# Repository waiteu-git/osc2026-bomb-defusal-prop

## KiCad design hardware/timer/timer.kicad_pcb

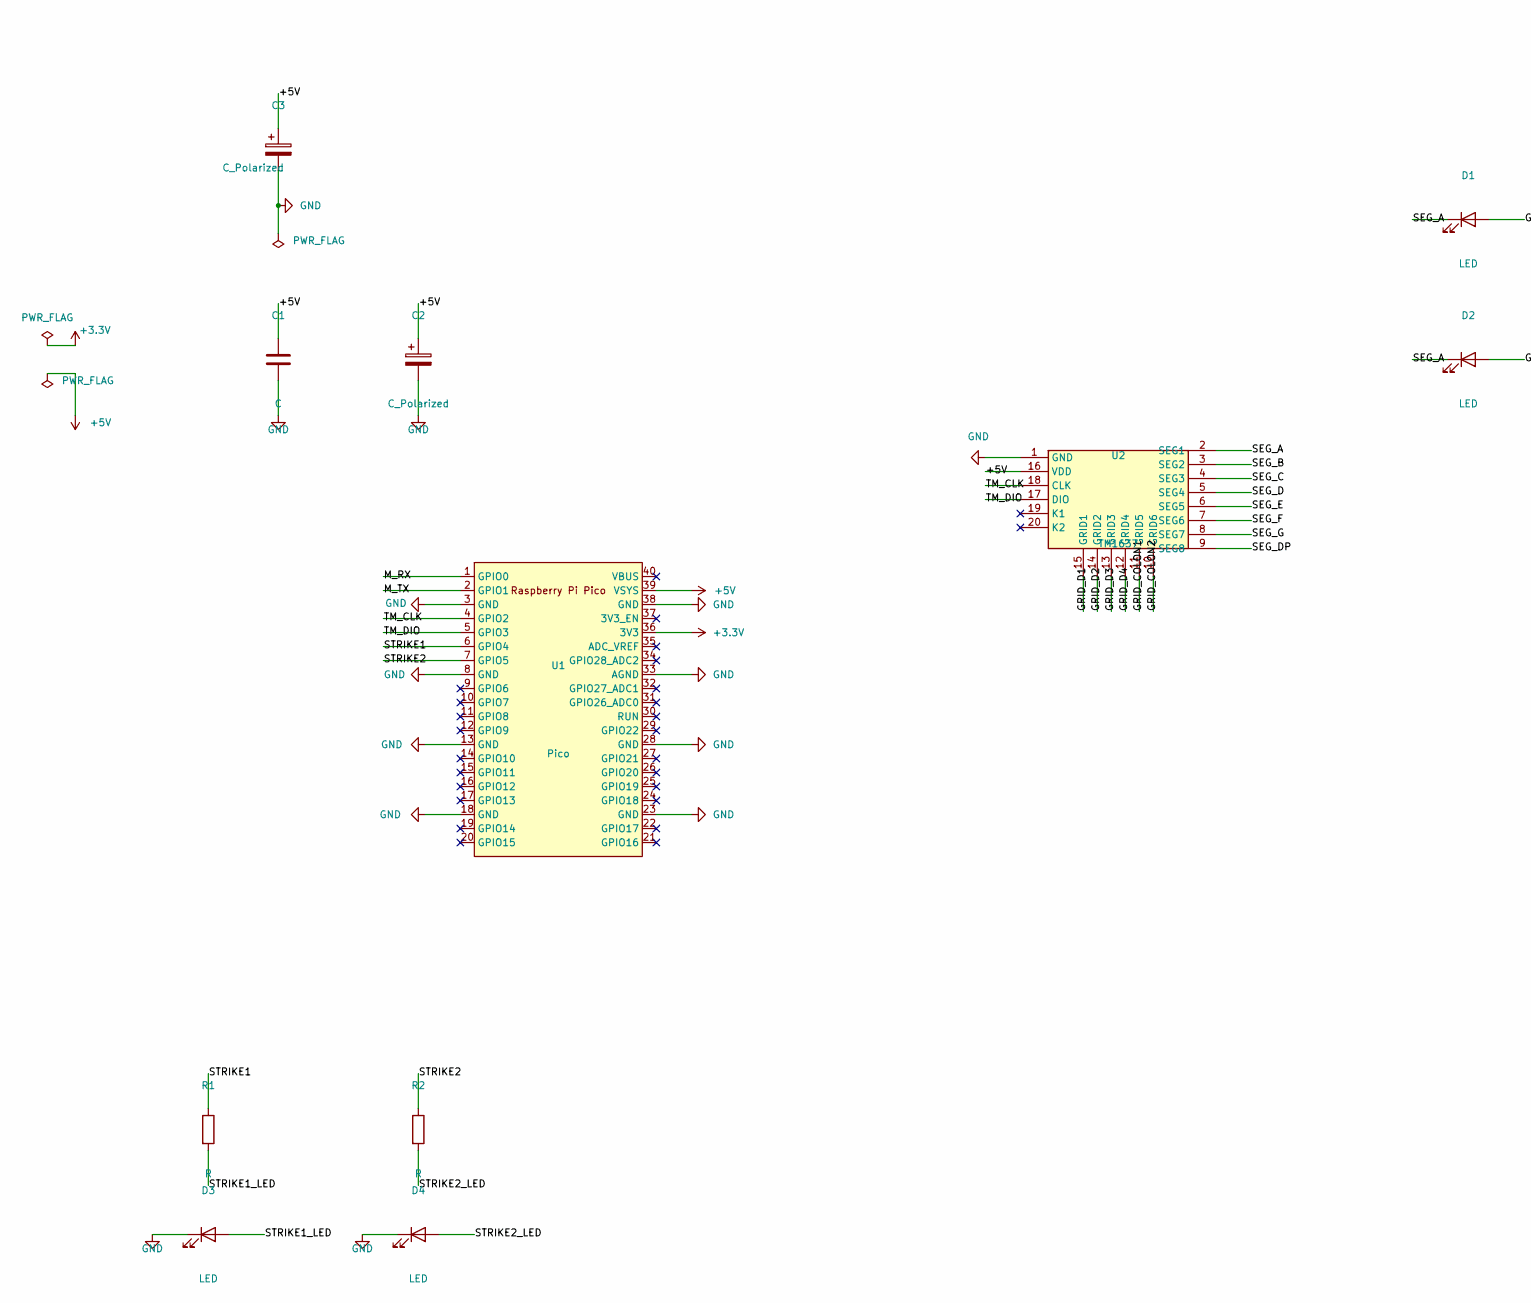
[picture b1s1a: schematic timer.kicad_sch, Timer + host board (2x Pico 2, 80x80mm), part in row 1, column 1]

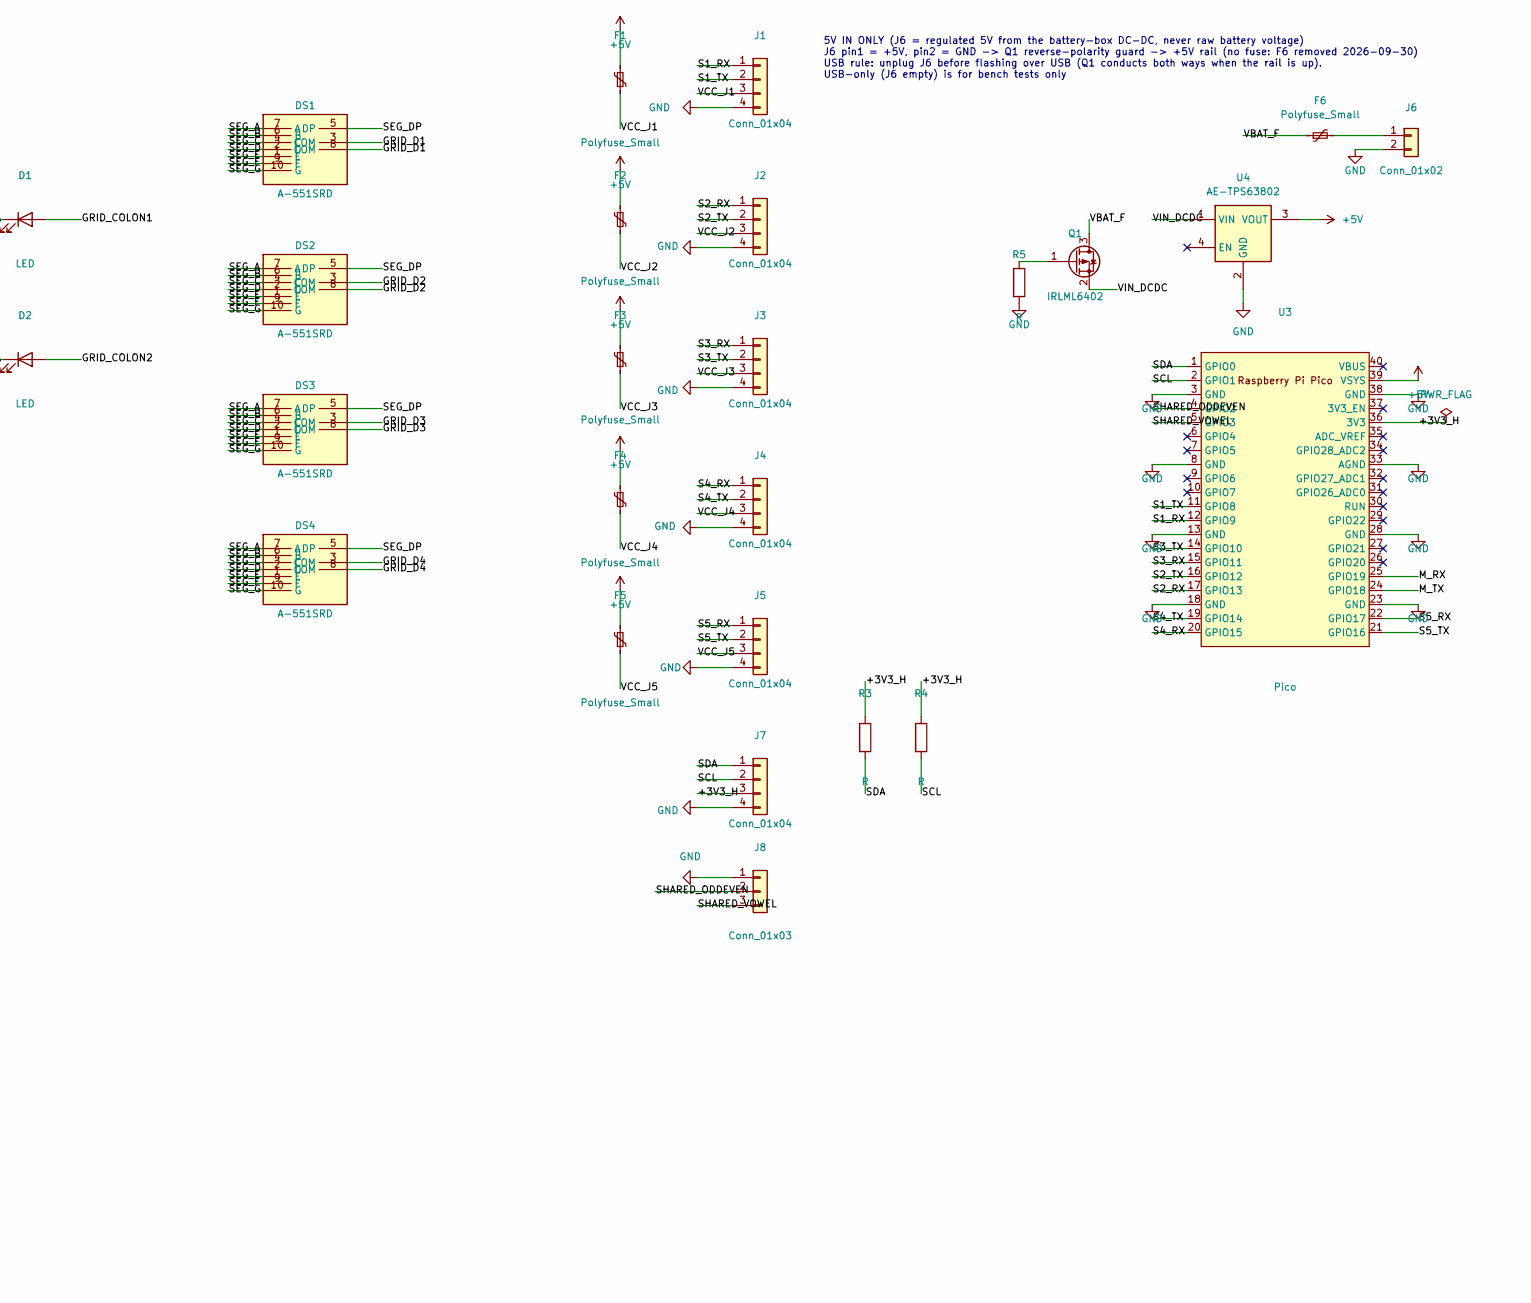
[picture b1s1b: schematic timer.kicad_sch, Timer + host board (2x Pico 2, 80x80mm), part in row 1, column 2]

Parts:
C1: C; C_Disc_D5.0mm_W2.5mm_P2.50mm
C2: C_Polarized; CP_Radial_D5.0mm_P2.00mm
C3: C_Polarized; CP_Radial_D8.0mm_P3.50mm
D1, D2: LED; LED_D3.0mm
D3, D4: LED; LED_D5.0mm
DS1, DS2, DS3, DS4: A-551SRD
F1, F2, F3, F4, F5: Polyfuse_Small; MF-RX030_Radial_P5.10mm
F6: Polyfuse_Small; MF-R185_Radial_P5.10mm
J1, J2, J3, J4, J5, J7: Conn_01x04; JST_XH_B4B-XH-A_1x04_P2.50mm_Vertical
J6: Conn_01x02; JST_XH_B2B-XH-A_1x02_P2.50mm_Vertical
J8: Conn_01x03; JST_XH_B3B-XH-A_1x03_P2.50mm_Vertical
Q1: IRLML6402; SOT-23
R1, R2: R; R_Axial_DIN0207_L6.3mm_D2.5mm_P10.16mm_Horizontal
R3, R4, R5: R; R_Axial_DIN0207_L6.3mm_D2.5mm_P2.54mm_Vertical
U1, U3: Pico; RPi_Pico_TH_Headers
U2: TM1637; DIP-20_W7.62mm
U4: AE-TPS63802

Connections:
+3.3V: U1.36 (3V3)
+5V: C1.1, C2.1, C3.1, F1.1, F2.1, F3.1, F4.1, F5.1, U1.39 (VSYS), U2.16 (VDD), U3.39 (VSYS), U4.3 (VOUT)
/+3V3_H: J7.3, R3.1, R4.1, U3.36 (3V3)
/GRID_COLON1: D1.2 (A), U2.11 (GRID5)
/GRID_COLON2: D2.2 (A), U2.10 (GRID6)
/GRID_D1: DS1.3 (COM), DS1.8 (COM), U2.15 (GRID1)
/GRID_D2: DS2.3 (COM), DS2.8 (COM), U2.14 (GRID2)
/GRID_D3: DS3.3 (COM), DS3.8 (COM), U2.13 (GRID3)
/GRID_D4: DS4.3 (COM), DS4.8 (COM), U2.12 (GRID4)
/M_RX: U1.1 (GPIO0), U3.25 (GPIO19)
/M_TX: U1.2 (GPIO1), U3.24 (GPIO18)
/S1_RX: J1.1, U3.12 (GPIO9)
/S1_TX: J1.2, U3.11 (GPIO8)
/S2_RX: J2.1, U3.17 (GPIO13)
/S2_TX: J2.2, U3.16 (GPIO12)
/S3_RX: J3.1, U3.15 (GPIO11)
/S3_TX: J3.2, U3.14 (GPIO10)
/S4_RX: J4.1, U3.20 (GPIO15)
/S4_TX: J4.2, U3.19 (GPIO14)
/S5_RX: J5.1, U3.22 (GPIO17)
/S5_TX: J5.2, U3.21 (GPIO16)
/SCL: J7.2, R4.2, U3.2 (GPIO1)
/SDA: J7.1, R3.2, U3.1 (GPIO0)
/SEG_A: D1.1 (K), D2.1 (K), DS1.7 (A), DS2.7 (A), DS3.7 (A), DS4.7 (A), U2.2 (SEG1)
/SEG_B: DS1.6 (B), DS2.6 (B), DS3.6 (B), DS4.6 (B), U2.3 (SEG2)
/SEG_C: DS1.4 (C), DS2.4 (C), DS3.4 (C), DS4.4 (C), U2.4 (SEG3)
/SEG_D: DS1.2 (D), DS2.2 (D), DS3.2 (D), DS4.2 (D), U2.5 (SEG4)
/SEG_DP: DS1.5 (DP), DS2.5 (DP), DS3.5 (DP), DS4.5 (DP), U2.9 (SEG8)
/SEG_E: DS1.1 (E), DS2.1 (E), DS3.1 (E), DS4.1 (E), U2.6 (SEG5)
/SEG_F: DS1.9 (F), DS2.9 (F), DS3.9 (F), DS4.9 (F), U2.7 (SEG6)
/SEG_G: DS1.10 (G), DS2.10 (G), DS3.10 (G), DS4.10 (G), U2.8 (SEG7)
/SHARED_ODDEVEN: J8.2, U3.4 (GPIO2)
/SHARED_VOWEL: J8.3, U3.5 (GPIO3)
/STRIKE1: R1.1, U1.6 (GPIO4)
/STRIKE1_LED: D3.2 (A), R1.2
/STRIKE2: R2.1, U1.7 (GPIO5)
/STRIKE2_LED: D4.2 (A), R2.2
/TM_CLK: U1.4 (GPIO2), U2.18 (CLK)
/TM_DIO: U1.5 (GPIO3), U2.17 (DIO)
/VBAT_F: F6.1, Q1.3 (D)
/VCC_J1: F1.2, J1.3
/VCC_J2: F2.2, J2.3
/VCC_J3: F3.2, J3.3
/VCC_J4: F4.2, J4.3
/VCC_J5: F5.2, J5.3
/VIN_DCDC: Q1.2 (S), U4.1 (VIN)
GND: C1.2, C2.2, C3.2, D3.1 (K), D4.1 (K), J1.4, J2.4, J3.4, J4.4, J5.4, J6.2, J7.4, J8.1, R5.2, U1.3 (GND), U1.8 (GND), U1.13 (GND), U1.18 (GND), U1.23 (GND), U1.28 (GND), U1.33 (AGND), U1.38 (GND), U2.1 (GND), U3.3 (GND), U3.8 (GND), U3.13 (GND), U3.18 (GND), U3.23 (GND), U3.28 (GND), U3.33 (AGND), U3.38 (GND), U4.2 (GND)
unnamed: F6.2, J6.1
unnamed: Q1.1 (G), R5.1

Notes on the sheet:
5V IN ONLY (J6 = regulated 5V from the battery-box DC-DC, never raw battery voltage) J6 pin1 = +5V, pin2 = GND -> Q1 reverse-polarity guard -> +5V rail (no fuse: F6 removed 2026-09-30) USB rule: unplug J6 before flashing over USB (Q1 conducts both ways when the rail is up). USB-only (J6 empty) is f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

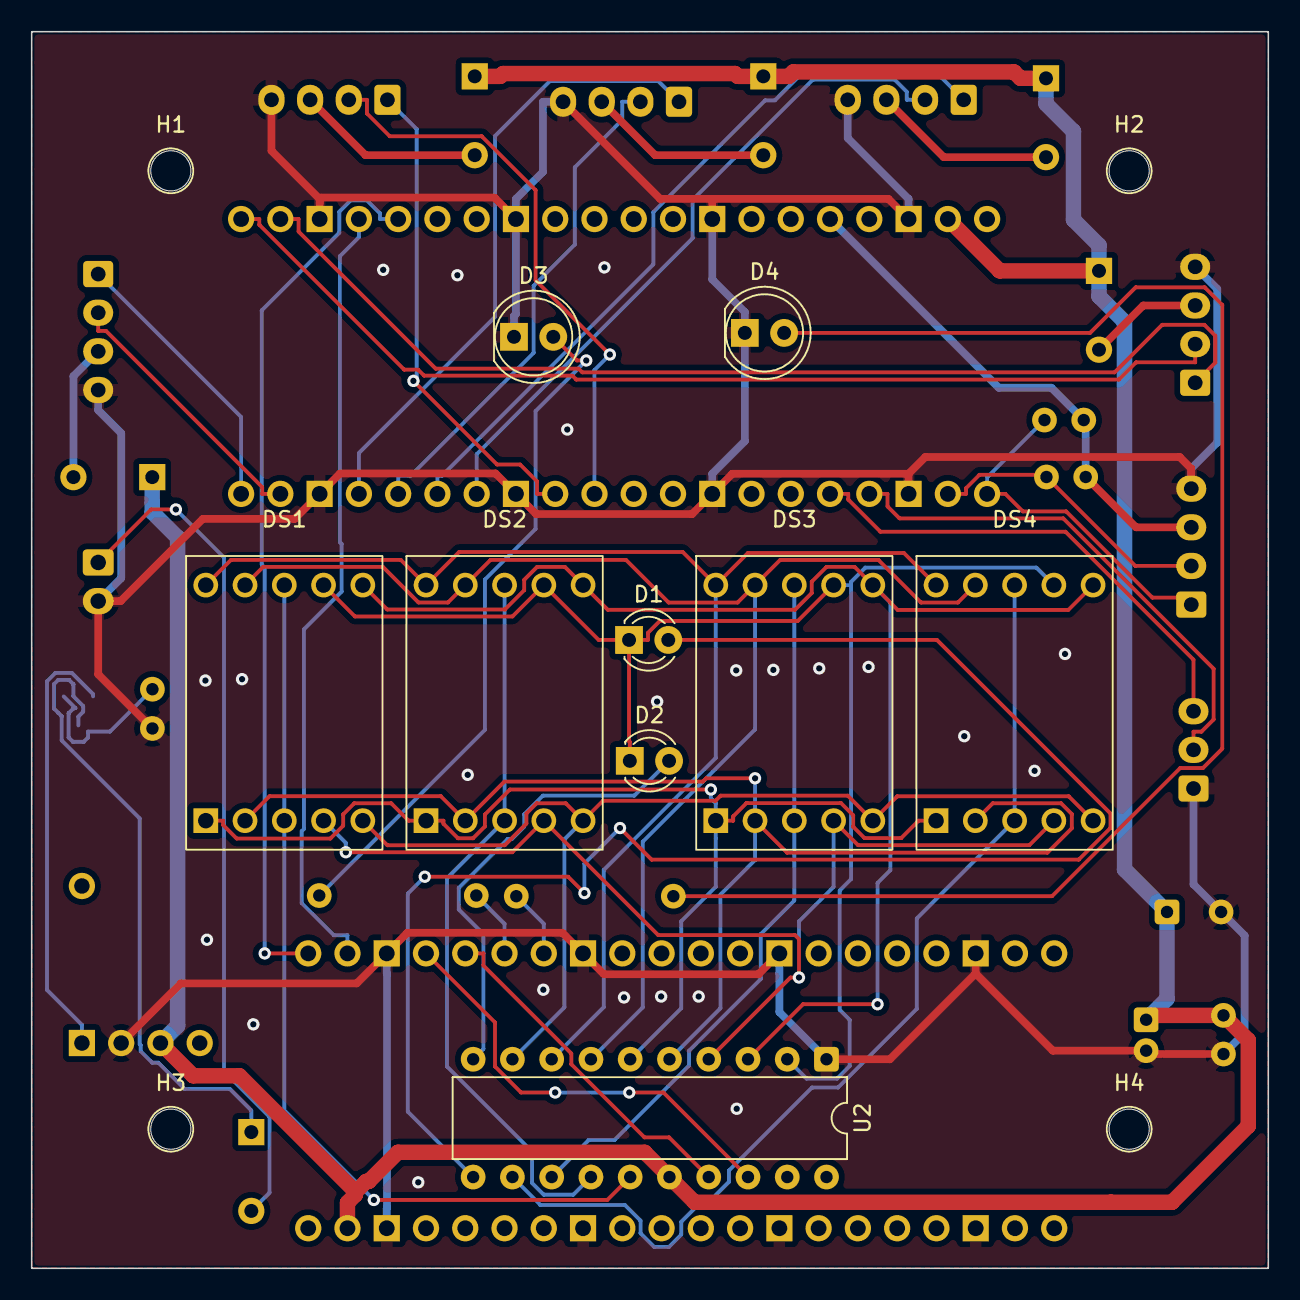
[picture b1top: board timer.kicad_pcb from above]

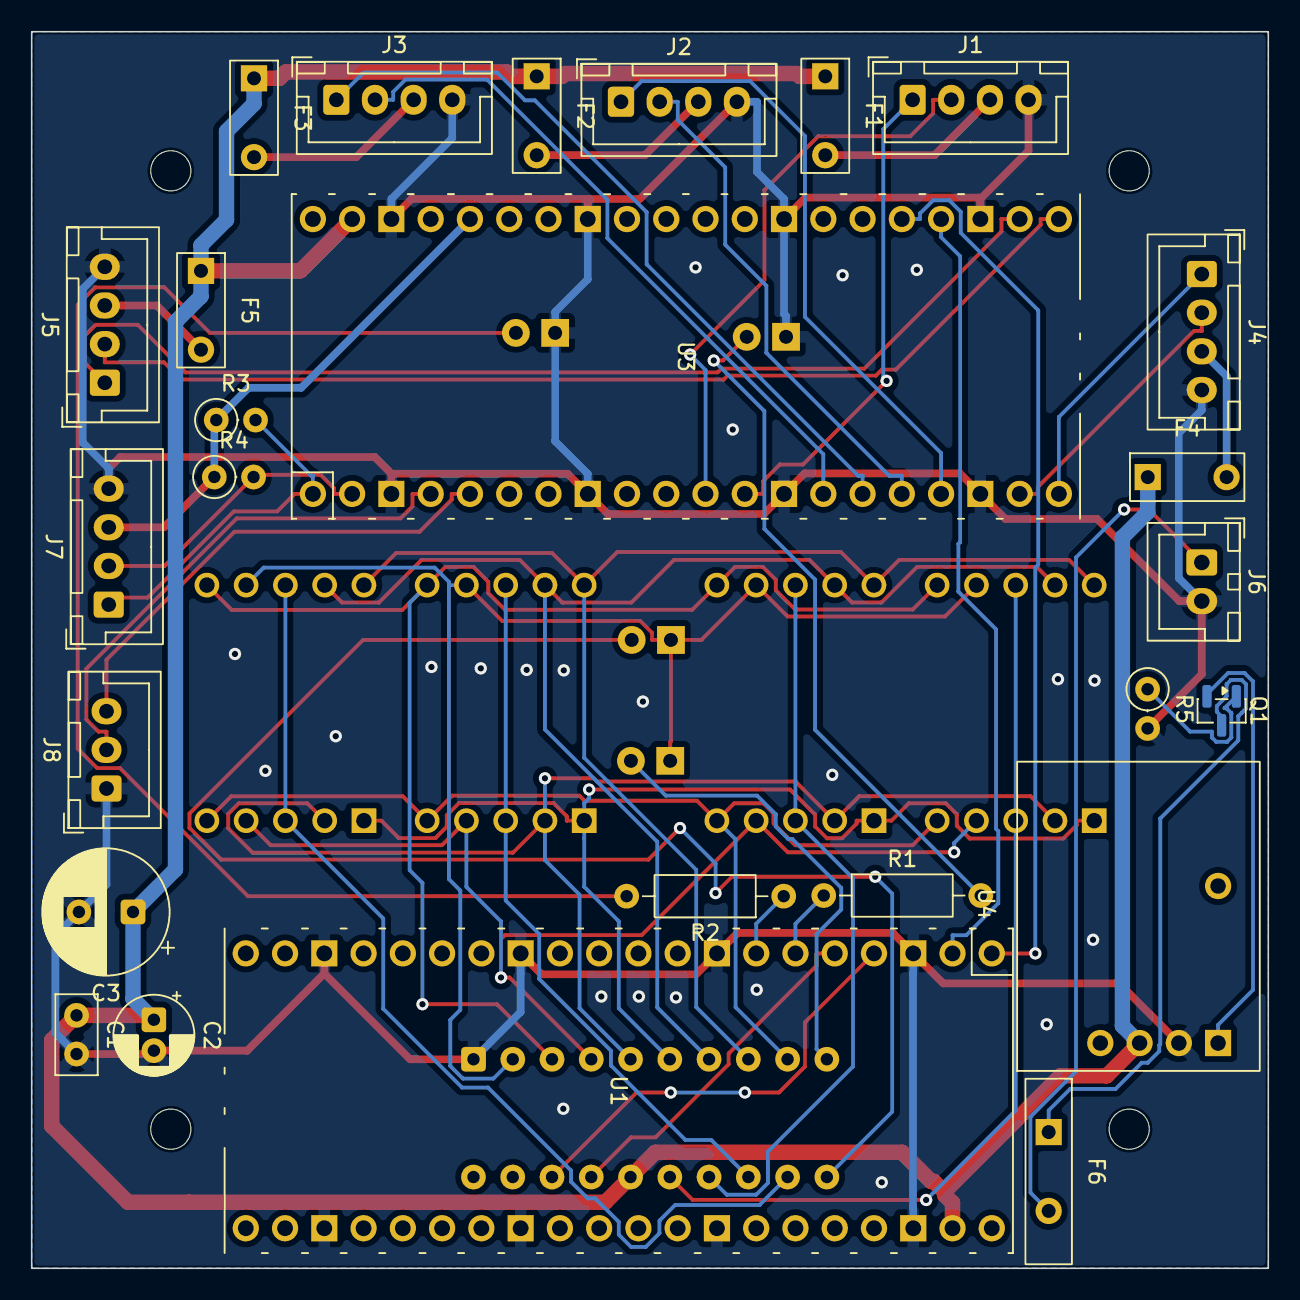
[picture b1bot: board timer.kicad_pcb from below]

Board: 2 copper layers, 80.0 x 80.0 mm, 39 parts (26 on the bottom side), 48 nets.

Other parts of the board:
H1, H2, H3, H4: M2.6 hole (dia 2.6mm); MountingHole_2.6mm

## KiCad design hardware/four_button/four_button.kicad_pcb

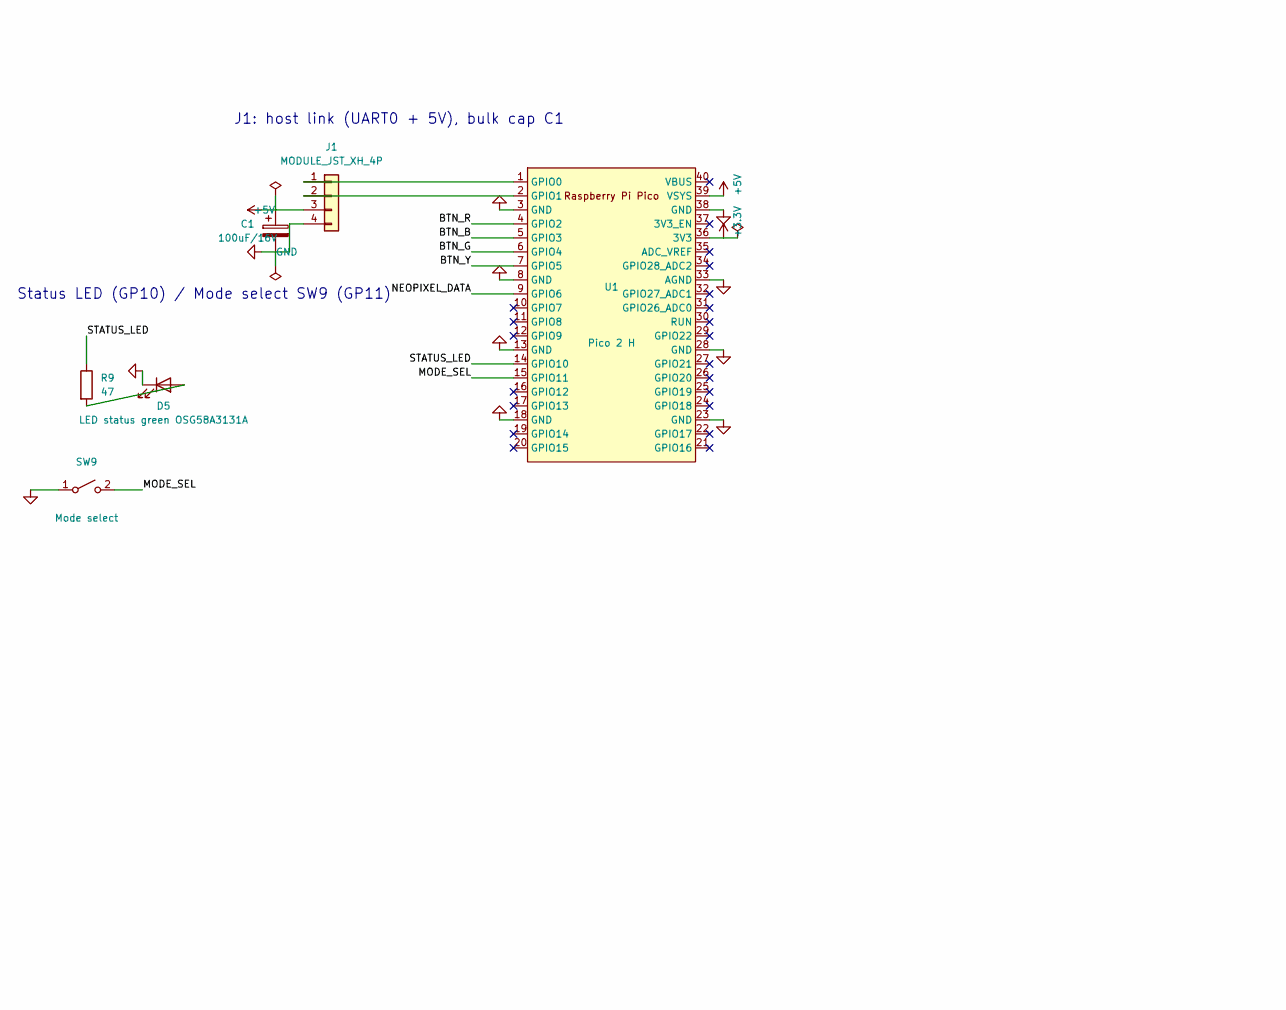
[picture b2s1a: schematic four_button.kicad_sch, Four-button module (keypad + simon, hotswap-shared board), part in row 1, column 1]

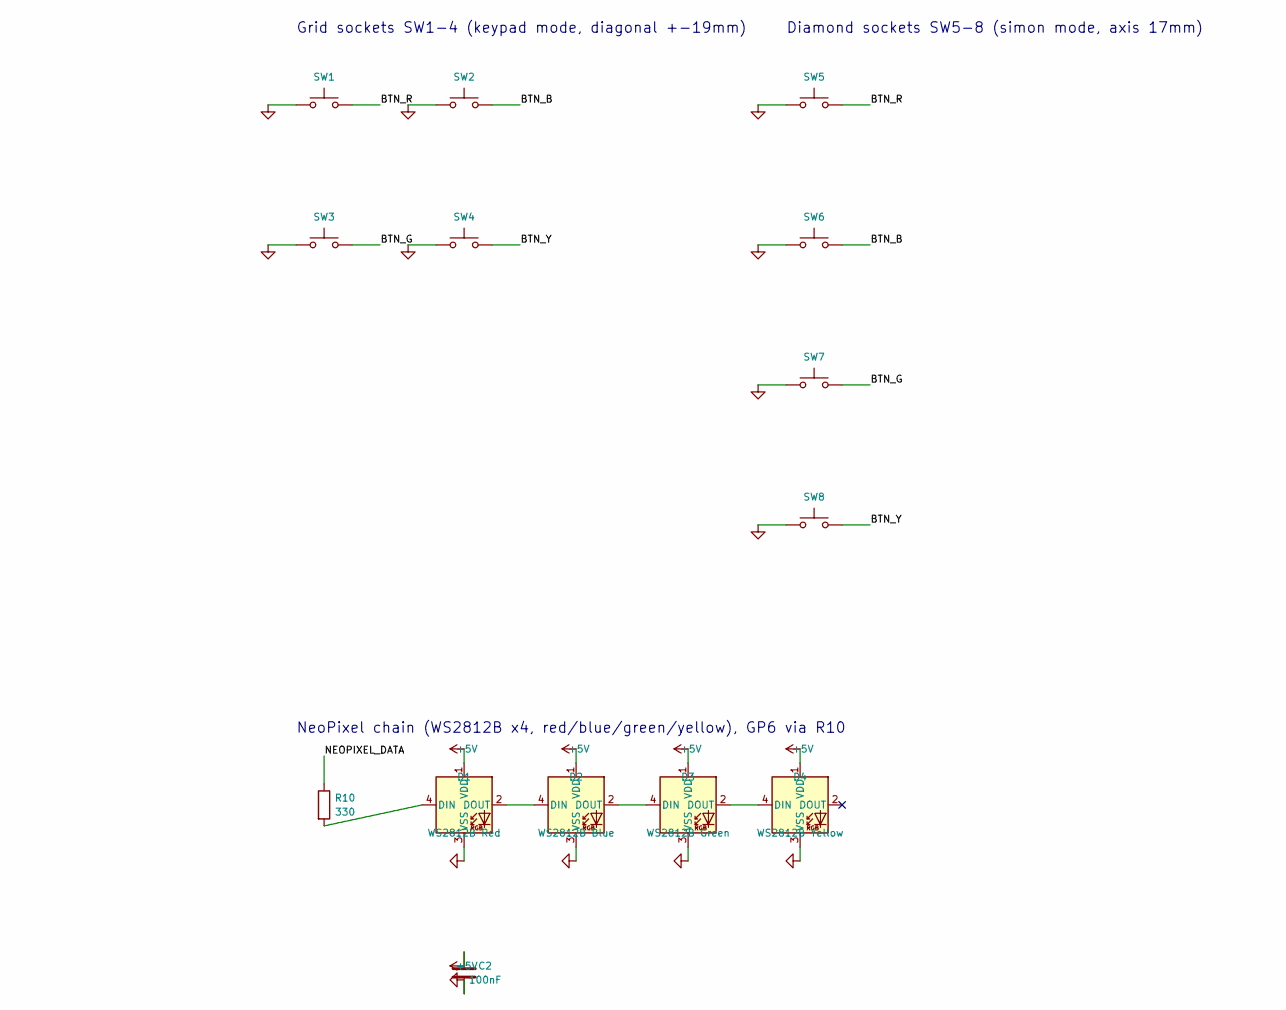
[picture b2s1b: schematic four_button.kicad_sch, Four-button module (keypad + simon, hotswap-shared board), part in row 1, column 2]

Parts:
C1: 100uF/16V; CP_Radial_D6.3mm_P2.50mm
C2: 100nF; C_Disc_D3.0mm_W2.0mm_P2.50mm
D1: WS2812B Red; LED_WS2812B_PLCC4_5.0x5.0mm_P3.2mm
D2: WS2812B Blue; LED_WS2812B_PLCC4_5.0x5.0mm_P3.2mm
D3: WS2812B Green; LED_WS2812B_PLCC4_5.0x5.0mm_P3.2mm
D4: WS2812B Yellow; LED_WS2812B_PLCC4_5.0x5.0mm_P3.2mm
D5: LED status green OSG58A3131A; LED_D3.0mm
J1: MODULE_JST_XH_4P; JST_XH_B4B-XH-A_1x04_P2.50mm_Vertical
R9: 47; R_Axial_DIN0207_L6.3mm_D2.5mm_P7.62mm_Horizontal
R10: 330; R_Axial_DIN0207_L6.3mm_D2.5mm_P7.62mm_Horizontal
SW1, SW2, SW3, SW4, SW5, SW6, SW7, SW8: Kailh_socket_MX
SW9: Mode select; SW_Slide_2P
U1: Pico 2 H; RPi_Pico_TH_Headers

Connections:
+3.3V: U1.36 (3V3)
+5V: C1.1, C2.1, D1.1 (VDD), D2.1 (VDD), D3.1 (VDD), D4.1 (VDD), J1.3, U1.39 (VSYS)
/BTN_B: SW2.2, SW6.2, U1.5 (GPIO3)
/BTN_G: SW3.2, SW7.2, U1.6 (GPIO4)
/BTN_R: SW1.2, SW5.2, U1.4 (GPIO2)
/BTN_Y: SW4.2, SW8.2, U1.7 (GPIO5)
/MODE_SEL: SW9.2 (B), U1.15 (GPIO11)
/NEOPIXEL_DATA: R10.1, U1.9 (GPIO6)
/STATUS_LED: R9.1, U1.14 (GPIO10)
GND: C1.2, C2.2, D1.3 (VSS), D2.3 (VSS), D3.3 (VSS), D4.3 (VSS), D5.1 (K), J1.4, SW1.1, SW2.1, SW3.1, SW4.1, SW5.1, SW6.1, SW7.1, SW8.1, SW9.1 (A), U1.3 (GND), U1.8 (GND), U1.13 (GND), U1.18 (GND), U1.23 (GND), U1.28 (GND), U1.33 (AGND), U1.38 (GND)
unnamed: D1.4 (DIN), R10.2
unnamed: D1.2 (DOUT), D2.4 (DIN)
unnamed: D2.2 (DOUT), D3.4 (DIN)
unnamed: D3.2 (DOUT), D4.4 (DIN)
unnamed: D5.2 (A), R9.2
unnamed: J1.1, U1.1 (GPIO0)
unnamed: J1.2, U1.2 (GPIO1)

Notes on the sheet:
J1: host link (UART0 + 5V), bulk cap C1
Grid sockets SW1-4 (keypad mode, diagonal +-19mm)
Diamond sockets SW5-8 (simon mode, axis 17mm)
NeoPixel chain (WS2812B x4, red/blue/green/yellow), GP6 via R10
Status LED (GP10) / Mode select SW9 (GP11)

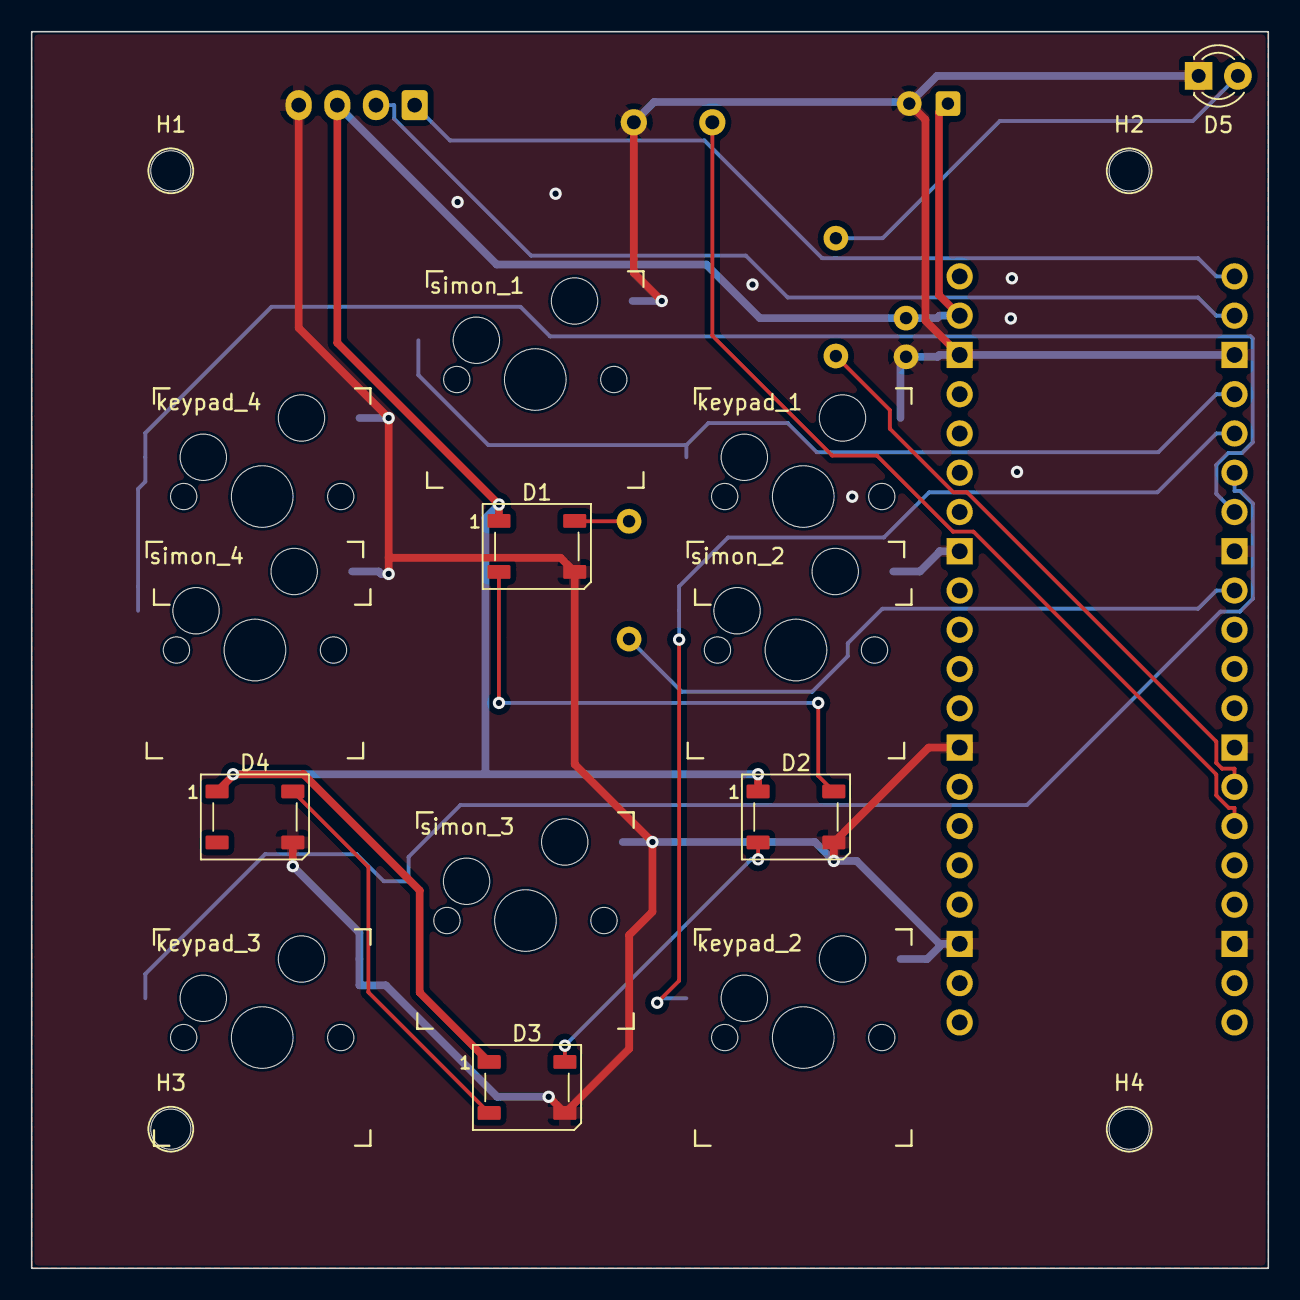
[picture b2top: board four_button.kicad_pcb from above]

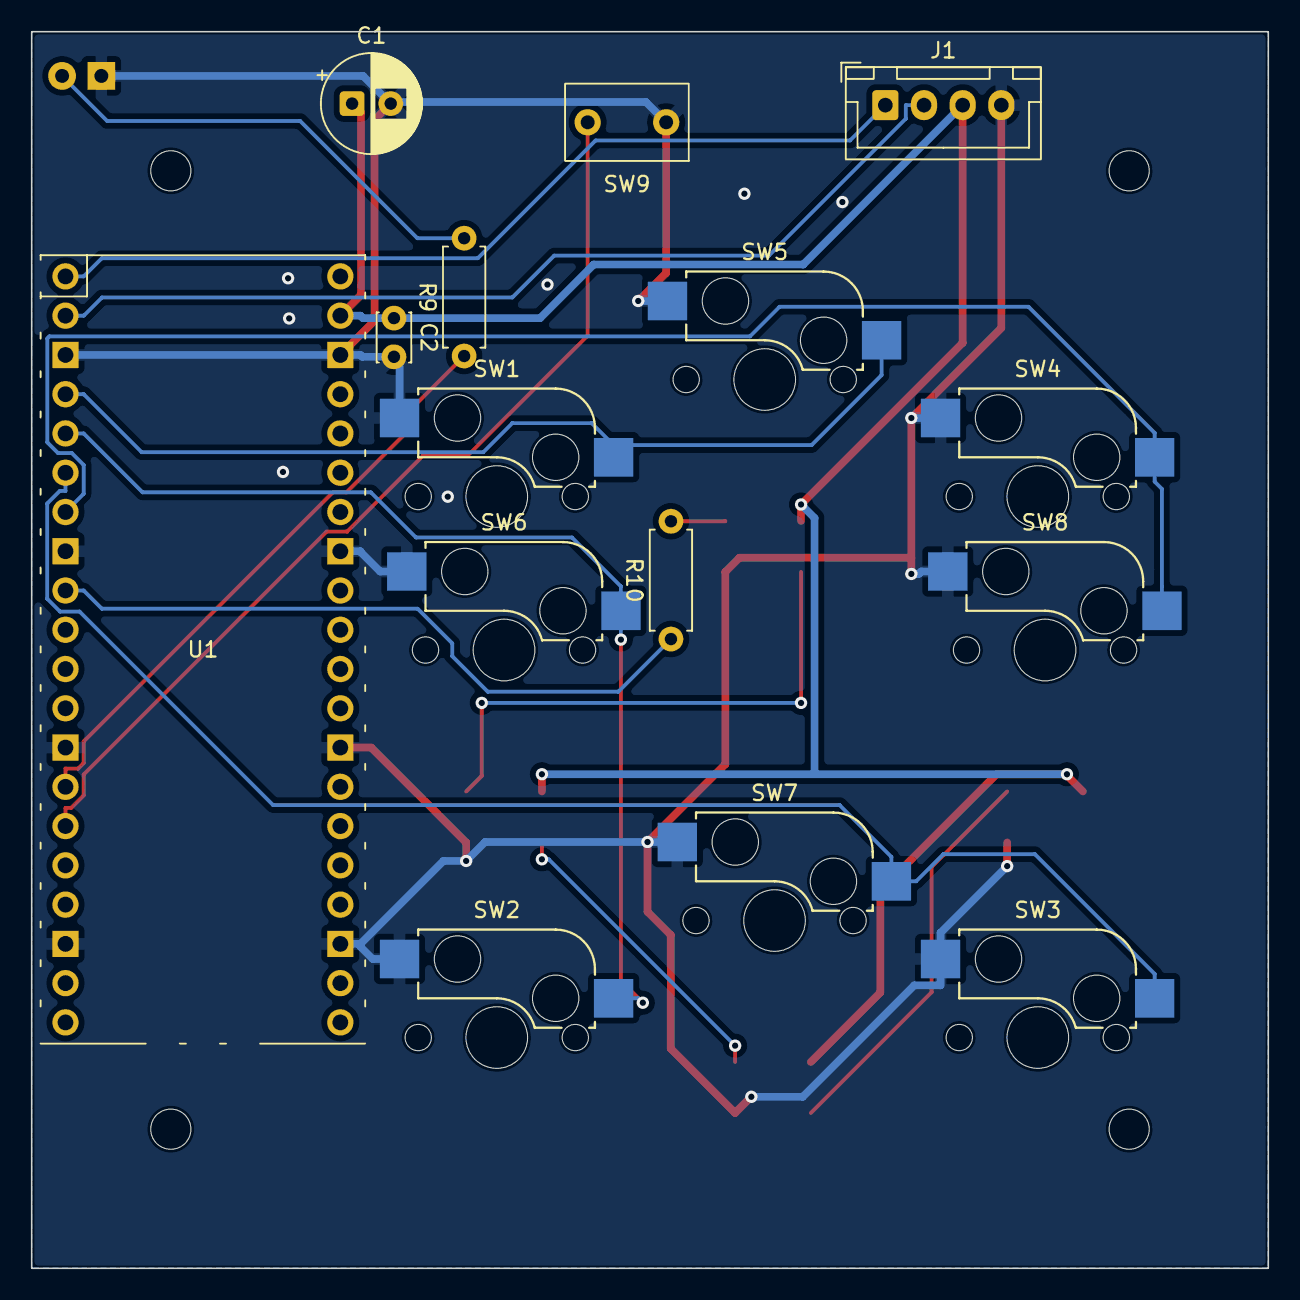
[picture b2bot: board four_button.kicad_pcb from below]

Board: 2 copper layers, 80.0 x 80.0 mm, 24 parts (7 on the bottom side), 16 nets.

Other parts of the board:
H1, H2, H3, H4: M2.6 hole (dia 2.6mm); MountingHole_2.6mm

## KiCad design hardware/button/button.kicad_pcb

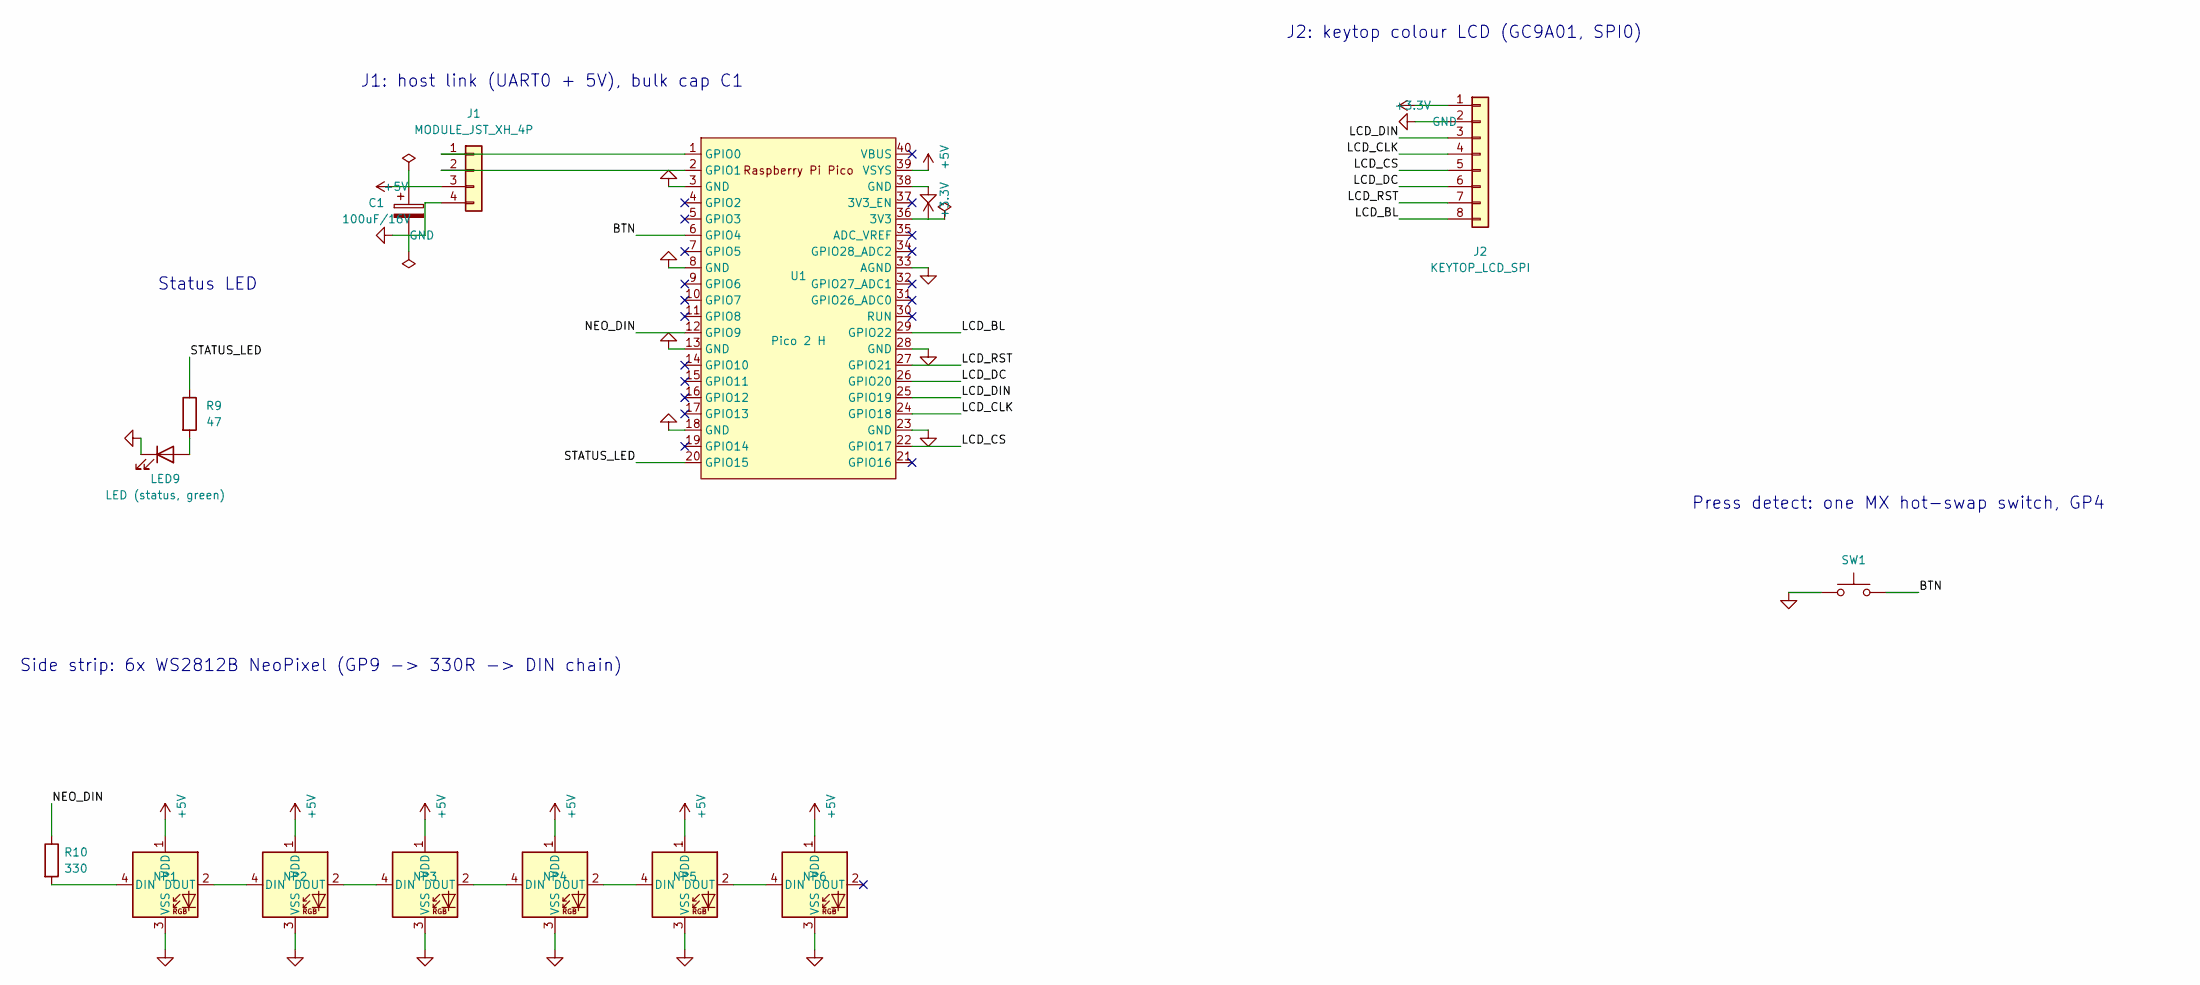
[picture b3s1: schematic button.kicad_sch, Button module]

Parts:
C1: 100uF/16V; CP_Radial_D6.3mm_P2.50mm
J1: MODULE_JST_XH_4P; JST_XH_B4B-XH-A_1x04_P2.50mm_Vertical
J2: KEYTOP_LCD_SPI; PinHeader_1x08_P2.54mm_Vertical
LED9: LED (status, green); LED_D3.0mm
NP1, NP2, NP3, NP4, NP5, NP6: WS2812B; LED_WS2812B_PLCC4_5.0x5.0mm_P3.2mm
R9: 47; R_Axial_DIN0207_L6.3mm_D2.5mm_P7.62mm_Horizontal
R10: 330; R_Axial_DIN0207_L6.3mm_D2.5mm_P7.62mm_Horizontal
SW1: SW_Push; Kailh_socket_MX
U1: Pico 2 H; RPi_Pico_TH_Headers

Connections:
+3.3V: J2.1, U1.36 (3V3)
+5V: C1.1, J1.3, NP1.1 (VDD), NP2.1 (VDD), NP3.1 (VDD), NP4.1 (VDD), NP5.1 (VDD), NP6.1 (VDD), U1.39 (VSYS)
/BTN: SW1.2, U1.6 (GPIO4)
/LCD_BL: J2.8, U1.29 (GPIO22)
/LCD_CLK: J2.4, U1.24 (GPIO18)
/LCD_CS: J2.5, U1.22 (GPIO17)
/LCD_DC: J2.6, U1.26 (GPIO20)
/LCD_DIN: J2.3, U1.25 (GPIO19)
/LCD_RST: J2.7, U1.27 (GPIO21)
/NEO_DIN: R10.1, U1.12 (GPIO9)
/STATUS_LED: R9.1, U1.20 (GPIO15)
GND: C1.2, J1.4, J2.2, LED9.1 (K), NP1.3 (VSS), NP2.3 (VSS), NP3.3 (VSS), NP4.3 (VSS), NP5.3 (VSS), NP6.3 (VSS), SW1.1, U1.3 (GND), U1.8 (GND), U1.13 (GND), U1.18 (GND), U1.23 (GND), U1.28 (GND), U1.33 (AGND), U1.38 (GND)
unnamed: J1.1, U1.1 (GPIO0)
unnamed: J1.2, U1.2 (GPIO1)
unnamed: LED9.2 (A), R9.2
unnamed: NP1.4 (DIN), R10.2
unnamed: NP1.2 (DOUT), NP2.4 (DIN)
unnamed: NP2.2 (DOUT), NP3.4 (DIN)
unnamed: NP3.2 (DOUT), NP4.4 (DIN)
unnamed: NP4.2 (DOUT), NP5.4 (DIN)
unnamed: NP5.2 (DOUT), NP6.4 (DIN)

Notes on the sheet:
J1: host link (UART0 + 5V), bulk cap C1
Side strip: 6x WS2812B NeoPixel (GP9 -> 330R -> DIN chain)
Press detect: one MX hot-swap switch, GP4
J2: keytop colour LCD (GC9A01, SPI0)
Status LED
